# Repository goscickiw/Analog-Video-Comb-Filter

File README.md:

# Analog-Video-Comb-Filter
Analog Composite Video to S-Video comb filter board using SAA4960, SAA4961 or SAA4963 integrated circuit.

## **WARNING**
**This project uses end-of-life components that are no longer manufactured. If you want to build this, make sure that you can obtain all components before starting. Used or new-old-stock parts can sometimes be found online.**

## Description

This is a fully analog alternative to digital comb filters such as Extron YCS Transcoder or YCS 100. [That doesn't mean it will give better results though](#image-comparison---no-filter-lc-filter-and-comb-filters). I just made it because I didn't find any fully analog device like that on the market and I wanted one.

The comb filter is used to convert a composite video signal into an S-Video (Y/C) signal. Comb filters are much better than passive LC filters usually built into composite video displays, as they can preserve the frequencies of luminance that overlap with chrominance, providing higher image detail while removing dot crawl, and remove those overlapping luminance frequencies from the chrominance signal which reduces color artifacts.

When using the SAA4960 integrated circuit, PAL B, D, G, H and I systems are supported.

SAA4961 provides aditional support for PAL M, N and NTSC M systems.

When using the SAA4963 integrated circuit, only the NTSC M system is supported.

The board is designed to fit inside a KRADEX Z-76 enclosure.

### Circuit description

A composite video signal is fed in through an RCA connector (J4). The signal is terminated with a 75 ohm resistor and fed to U3 (or U7), U4 and U6 through 100 nF capacitors.

The LM1881 sync separator (U6) uses the composite video signal to generate a burst gate signal. The burst gate signal passes through a 74HC04 inverter (U5) to the MC44144 subcarrier PLL (U4).

U4 uses the composite video signal and the burst gate signal to generate a subcarrier frequency synchronized to the colorburst of the composite video signal. This subcarrier signal is then passed to the FSC input of U3/U7.

The SAA4960/61/63 comb filter (U3 or U7) is fed with the composite video signal and the synchronized subcarrier signal. The jumpers SYS1 and SYS2 set the video standard, and the jumper LPF can be used to disable the input low-pass filter. This circuit outputs filtered luminance and chrominance signals and a delayed composite video passthrough signal (when using SAA4963, the CVBYP jumper has to be shorted to allow non-delayed composite video passthrough). Those signals are then fed to the output amplifiers.

The AD813 triple op-amp (U2) is used for the output amplifiers. The output signals from the SAA4960/61[^1] are DC-biased by around 1V, so a non-rail-to-rail op-amp like the AD813 is viable. The gain can be adjusted from approx. 1,5x to 2,5x with RV1, RV2 and RV3.

## Pictures

| Assembled rev.2 devices (PAL and NTSC)               | Completed, operating device in enclosure                     |
| ---------------------------------------------------- | ------------------------------------------------------------ |
|  |  |

### Image comparison - no filter, LC filter and comb filters

<table>
  <tr>
    <th width="50%">No filter</th>
    <th width="50%">LC filter</th>
  </tr>
  <tr>
    <td>Luminance detail is preserved, but dot crawl is visible across the entire picture.</td>
    <td>Dot crawl is mostly removed, but luminance loses some sharpness, and higher frequency luminance components (responsible for sharpness) are left in chrominance causing color artifacts.</td>
  </tr>
  <tr>
    <td></td>
    <td></td>
  </tr>
  <tr>
    <td></td>
    <td></td>
  </tr>
  <tr>
    <th>This analog comb filter</th>
    <th>MC141627 digital comb filter (for comparison, Extron YCS transcoder)</th>
  </tr>
  <tr>
    <td>Dot crawl is mostly removed and luminance sharpness is mostly preserved. Higher frequency luminance components are properly separated from chrominance.</td>
    <td>More effective than the analog comb filter.</td>
  </tr>
  <tr>
    <td></td>
    <td></td>
  </tr>
</table>

<details>
  <summary>Monochrome image comparison</summary>
  <table>
    <tr>
      <th width="50%">No filter</th>
      <th width="50%">LC filter</th>
    </tr>
    <tr>
      <td>Luminance detail is preserved, but dot crawl is visible in colored sections.</td>
      <td>Dot crawl is mostly removed, but luminance loses some sharpness.</td>
    </tr>
    <tr>
      <td></td>
      <td></td>
    </tr>
    <tr>
      <td></td>
      <td></td>
    </tr>
    <tr>
      <th>This analog comb filter</th>
      <th>MC141627 digital comb filter (for comparison, Extron YCS transcoder)</th>
    </tr>
    <tr>
      <td>Dot crawl is mostly removed and luminance sharpness is mostly preserved.</td>
      <td>More effective than the analog comb filter.</td>
    </tr>
    <tr>
      <td></td>
      <td></td>
    </tr>
  </table>
</details>

## LEDs

D1 shows that the device is receiving power.

D2 shows that the comb filter is operating (U3 is in COMB mode). I'm not sure if U3 will ever *not* be in COMB mode when used in this circuit, so this LED might be unnecessary. SAA4963 does not have the output needed by this LED, so if it is used, then R19, R20, D2 and Q1 can be left unpopulated.

## REFDL filter capacitors

When using SAA4960 or SAA4961, install C24 and C26, and leave C31 and C32 unpopulated.

When using SAA4963, install C31 and C32, and leave C24 and C26 unpopulated.

## Solder jumper settings

### Standard selection jumpers (SYS1, SYS2)

SAA4961 only. When using SAA4960, SYS1 and SYS2 jumpers should be left open. When using SAA4963, the jumpers are not connected.

Appropriate crystal for the subcarrier oscillator should be installed depending on the jumper setting. If the standard is going to be changed frequently, it may be possible to install a socket for the crystal, however it should be taken into account that MC44144 is sensitive to additional capacitance at the crystal.

| Standard      | SYS1  | SYS2  | Crystal required | 
| ------------- | ----- | ----- | ---------------- |
| PAL B/D/G/H/I | Open  | Open  | 17,734475 MHz    |
| PAL M         | Open  | Short | 14,302444 MHz    |
| PAL N         | Short | Open  | 14,328225 MHz    |
| NTSC M        | Short | Short | 14,31818 MHz     |

### Low pass filter jumper (LPF)

The SAA4960, SAA4961 and SAA4963 integrated circuits have a built-in low-pass filter on the composite video input. With SAA4960 and SAA4961, this filter can be disabled by shorting the LPF jumper, but it's recommended to leave it on. With SAA4963, the jumper is not connected and the filter is always on.

| LPF   | Filter mode     |
| ----- | --------------- |
| Open  | Filter enabled  |
| Short | Filter disabled |

### Composite video passthrough jumper (CVBYP)

SAA4963 doesn't have a composite video output, so the CVBYP jumper was provided for composite video passthrough. When the jumper is shorted, the video signal for composite video output is taken from pin 13 (composite video input) of SAA4963. The DC bias for the output amplifier is provided by the clamping circuit inside SAA4963. Do not install R12 to avoid additional load to the clamping circuit. This configuration has not been tested and may not work correctly. Leave the jumper open if shorting it causes issues for the comb filter.

**WARNING: This jumper must never be shorted if using SAA4960/61.**

| CVBYP | Usage                          |
| ----- | ------------------------------ |
| Open  | When using SAA4960 or SAA4961. |
| Short | When using SAA4963.            |

## Adjustment

After assembly, including setting the jumpers and installing the correct crystal depending on the analog video standard, the variable capacitor C17 will have to be adjusted so that the PLL locks correctly to the color subcarrier and the loop control voltage is centered.

Use the following procedure for adjustment:

1. Connect an EBU (for PAL) or SMPTE (for NTSC) color bar signal from a good quality reference source to the composite video input.
2. Connect a 10x oscillososcope probe to U4 pin 3 (phase detector output loop filter). Use AC coupling, 200 mV/div vertical scale, and 100 µs/div timebase.
3. Here are the reference pictures needed for the following steps:

<details>
  <summary>PAL waveforms</summary>
  <table>
    <tr>
      <th width="33%">Not locked</th>
      <th width="33%">Locked, not adjusted</th>
      <th width="33%">Best adjustment</th>
    </tr>
    <tr>
      <td></td>
      <td><br/></td>
      <td></td>
    </tr>
  </table>
</details>

<details>
  <summary>NTSC waveforms</summary>
  <table>
    <tr>
      <th width="33%">Not locked</th>
      <th width="33%">Locked, not adjusted</th>
      <th width="33%">Best adjustment</th>
    </tr>
    <tr>
      <td></td>
      <td><br/></td>
      <td></td>
    </tr>
  </table>
</details>

4. Follow the flow chart below:

```mermaid
flowchart LR
  A{Able to obtain waveform shown in <b>Best&nbsp;adjustment</b> by adjusting C17?} -- Yes --> B([PLL correctly adjusted.]);
  A -->|No| C{"PLL able to lock (one of <b>Locked,&nbsp;not&nbsp;adjusted</b> waveforms)?"};
  C -->|Yes| D{Does waveform resemble the <b>top</b> or <b>bottom</B> picture in <b>Locked,&nbsp;not&nbsp;adjusted</b>?};
  C -->|No| E["Measure frequency at U4 pin 1 (FSC output), and adjust C17 to get as close as possible to required frequency."];
  E --> F{Is the frequency higher or lower than required?};
  F -->|Higher| G[replace C17 with a higher max. value trim capacitor, or add a parallel capacitor.];
  F -->|Lower| H[replace C17 with a lower min. value trim capacitor.];
  D -->|Top| G;
  D -->|Bottom| H;
  G --> I[Adjust C17 and observe the waveform at U4 pin 3.] --> A;
  H --> I;
```

5. Set RV1, RV2, RV3 to center position. Connect the luminance, chrominance and composite outputs to an oscilloscope with 75 ohm load resistance. Luminance signal is preferred for oscilloscope trigger. Adjust RV1, RV2, RV3 to obtain the following:

<table>
  <tr>
    <th>Output</th>
    <th>Adjustment</th>
    <th>Measured value</th>
    <th>PAL</th>
    <th>NTSC</th>
  </tr>
  <tr>
    <td>Chrominance</td>
    <td>RV1</td>
    <td>Peak-peak <b>colorburst</b></td>
    <td>300 mV</td>
    <td>285,72 mV</td>
  </tr>
  <tr>
    <td>Luminance</td>
    <td>RV2</td>
    <td rowspan=2>Peak-peak voltage<br/>(sync level to 100% white level)</td>
    <td rowspan=2 colspan=2>1 V</td>
  </tr>
  <tr>
    <td>Composite</td>
    <td>RV3</td>
  </tr>
</table>

Readjustment is necessary if the crystal and the standard selection jumper settings are changed.

## Parts list

### Resistors

| Resistance | Power  | Qty |
| ---------- | ------ | --- |
| 47 Ω       | 0,25 W | 1   |
| 75 Ω       | 0,25 W | 4   |
| 470 Ω      | 0,25 W | 3   |
| 1 kΩ       | 0,25 W | 6   |
| 4,7 kΩ     | 0,25 W | 1   |
| 10 kΩ      | 0,25 W | 4   |
| 47 kΩ      | 0,25 W | 1   |
| 680 kΩ     | 0,25 W | 1   |

### Capacitors

| Capacitance | Pin pitch | Type                       | Qty |
| ----------- | --------- | -------------------------- | --- |
| 4-20 pF     | 5,08 mm   | Ceramic variable           | 1   |
| 470 pF      | 2,5 mm    | Ceramic                    | 1   |
| 1 nF        | 5 mm      | Ceramic                    | 1   |
| 100 nF      | 2,5 mm    | Ceramic                    | 18  |
| 100 μF      | 2 mm      | Electrolytic, ≥6,3V, ⌀5mm  | 6   |
| 100 μF      | 2 mm      | Electrolytic, ≥16V, ⌀5mm   | 1   |
| 220 μF      | 2,5 mm    | Electrolytic, ≥16V, ⌀6,3mm | 2   |

### Inductors

| Inductance | Max. Current | Exact part        | Qty |
| ---------- | ------------ | ----------------- | --- |
| 22 μH      | 0,285 A      | Ferrocore DLA22-N | 6   |

### Semiconductors

| Type           | Model     | Qty |
| -------------- | --------- | --- |
| LED            | 3mm Green | 1   |
| LED            | 3mm Red   | 1   |
| NPN Transistor | BC548     | 1   |

### Integrated circuits

| Model                         | Package                               | Qty |
| ----------------------------- | ------------------------------------- | --- |
| L7805                         | TO220                                 | 1   |
| AD813 or AD8044               | DIP14                                 | 1   |
| SAA4960 or SAA4961 or SAA4963 | DIP28 (SAA4960/61) or DIP20 (SAA4963) | 1   |
| MC44144                       | DIP8                                  | 1   |
| 74HC04                        | DIP14                                 | 1   |
| LM1881                        | DIP8                                  | 1   |

### Other

| Type               | Model                           | Qty |
| ------------------ | ------------------------------- | --- |
| Potentiometer      | PIHER PT10LH-1K                 | 3   |
| Crystal            | HC-49U, depends on video system | 1   |
| RCA Connector      | Keystone Electronics 973        | 2   |
| Mini-DIN Connector | MDC-204, unshielded             | 1   |
| DC Barrel Jack     | Generic 5,5/2,5mm               | 1   |
| Enclosure          | KRADEX Z-76                     | 1   |

## License

This work is licensed under CC BY-SA 4.0 license.

[^1]: SAA4963 has not been tested as I don't have one yet.

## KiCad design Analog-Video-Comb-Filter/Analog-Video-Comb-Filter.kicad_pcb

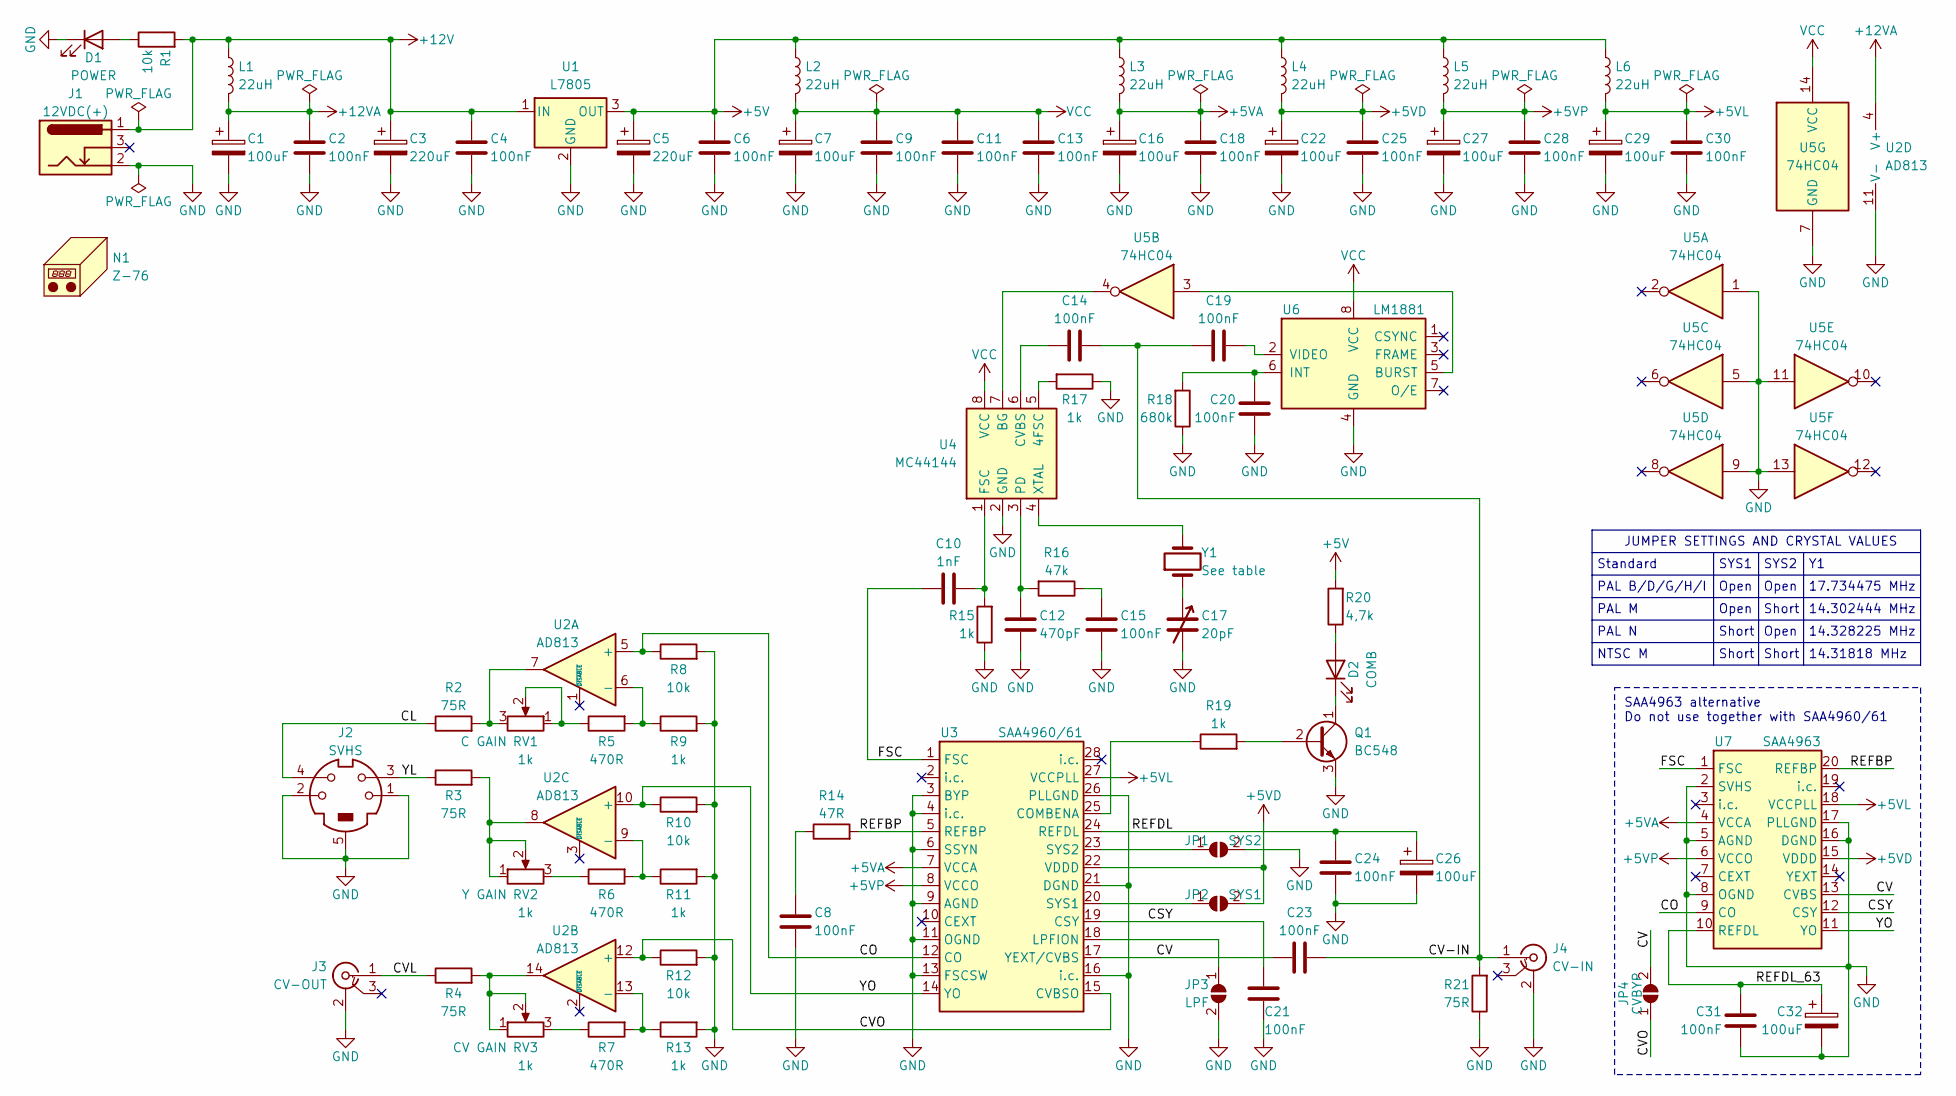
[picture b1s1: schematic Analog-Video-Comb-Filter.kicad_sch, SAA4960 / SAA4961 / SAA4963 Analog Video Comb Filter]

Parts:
C1, C7, C16, C22, C26, C27, C29, C32: 100uF; CP_Radial_D5.0mm_P2.00mm
C2, C4, C6, C8, C9, C11, C13, C14, C15, C18, C19, C20, C21, C23, C24, C25, C28, C30, C31: 100nF; C_Disc_D5.0mm_W2.5mm_P2.50mm
C3, C5: 220uF; CP_Radial_D6.3mm_P2.50mm
C10: 1nF; C_Disc_D5.0mm_W2.5mm_P5.00mm
C12: 470pF; C_Disc_D5.0mm_W2.5mm_P2.50mm
C17: 20pF; C_Trimmer_D6.0mm_P5.08mm
D1: POWER; LED_D3.0mm
D2: COMB; LED_D3.0mm
J1: 12VDC(+); BarrelJack_Horizontal
J2: SVHS; MDC-204
J3: CV-OUT; Keystone_973
J4: CV-IN; Keystone_973
JP1: SYS2; SolderJumper-2_P1.3mm_Open_RoundedPad1.0x1.5mm
JP2: SYS1; SolderJumper-2_P1.3mm_Open_RoundedPad1.0x1.5mm
JP3: LPF; SolderJumper-2_P1.3mm_Open_RoundedPad1.0x1.5mm
JP4: CVBYP; SolderJumper-2_P1.3mm_Open_RoundedPad1.0x1.5mm
L1, L2, L3, L5: 22uH; L_Axial_L5.3mm_D2.2mm_P7.62mm_Horizontal_Vishay_IM-1
L4, L6: 22uH; L_Axial_L5.3mm_D2.2mm_P2.54mm_Vertical_Vishay_IM-1
N1: Z-76
Q1: BC548; TO-92_Inline_Wide
R1, R8, R10, R12: 10k; R_Axial_DIN0207_L6.3mm_D2.5mm_P7.62mm_Horizontal
R2, R3, R4, R21: 75R; R_Axial_DIN0207_L6.3mm_D2.5mm_P7.62mm_Horizontal
R5, R6, R7: 470R; R_Axial_DIN0207_L6.3mm_D2.5mm_P7.62mm_Horizontal
R9, R11, R13, R15, R17, R19: 1k; R_Axial_DIN0207_L6.3mm_D2.5mm_P7.62mm_Horizontal
R14: 47R; R_Axial_DIN0207_L6.3mm_D2.5mm_P7.62mm_Horizontal
R16: 47k; R_Axial_DIN0207_L6.3mm_D2.5mm_P7.62mm_Horizontal
R18: 680k; R_Axial_DIN0207_L6.3mm_D2.5mm_P7.62mm_Horizontal
R20: 4,7k; R_Axial_DIN0207_L6.3mm_D2.5mm_P7.62mm_Horizontal
RV1, RV2, RV3: 1k; Potentiometer_Piher_PT-10-H01_Horizontal
U1: L7805; TO-220-3_Horizontal_TabDown
U2: AD813; DIP-14_W7.62mm_Socket
U3: SAA4960/61; DIP-28_W15.24mm_Socket
U4: MC44144; DIP-8_W7.62mm_Socket
U5: 74HC04; DIP-14_W7.62mm_Socket
U6: LM1881; DIP-8_W7.62mm_Socket
U7: SAA4963; DIP-20_W7.62mm_Socket
Y1: See table; Crystal_HC49-U_Vertical

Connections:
+5V: C5.1, C6.1, L2.1, L3.1, L4.2, L5.1, L6.2, R20.2, U1.3 (OUT)
+5VA: C16.1, C18.1, L3.2, U3.7 (VCCA), U7.4 (VCCA)
+5VD: C22.1, C25.1, JP2.2 (B), L4.1, U3.22 (VDDD), U7.15 (VDDD)
+5VL: C29.1, C30.1, L6.1, U3.27 (VCCPLL), U7.18 (VCCPLL)
+5VP: C27.1, C28.1, L5.2, U3.8 (VCCO), U7.6 (VCCO)
+12V: C3.1, C4.1, J1.1, L1.1, R1.2, U1.1 (IN)
+12VA: C1.1, C2.1, L1.2, U2.4 (V+)
/CL: J2.4, R2.1
/CO: R8.1, U2.5 (+), U3.12 (CO), U7.9 (CO)
/CSY: C21.1, U3.19 (CSY), U7.12 (CSY)
/CV: C23.1, JP4.2 (B), U3.17 (YEXT/CVBS), U7.13 (CVBS)
/CV-IN: C14.2, C19.1, C23.2, J4.1 (In), R21.2
/CVL: J3.1 (In), R4.1
/CVO: JP4.1 (A), R12.1, U2.12 (+), U3.15 (CVBSO)
/FSC: C10.1, U3.1 (FSC), U7.1 (FSC)
/REFBP: R14.2, U3.5 (REFBP), U7.20 (REFBP)
/REFDL: C24.1, C26.1, U3.24 (REFDL)
/REFDL_63: C31.1, C32.1, U7.10 (REFDL)
/YL: J2.3, R3.1
/YO: R10.1, U2.10 (+), U3.14 (YO), U7.11 (YO)
GND: C1.2, C2.2, C3.2, C4.2, C5.2, C6.2, C7.2, C8.2, C9.2, C11.2, C12.2, C13.2, C15.2, C16.2, C17.2, C18.2, C20.2, C21.2, C22.2, C24.2, C25.2, C26.2, C27.2, C28.2, C29.2, C30.2, C31.2, C32.2, D1.1 (K), J1.2, J2.1, J2.2, J2.5, J3.2 (Ext), J4.2 (Ext), JP1.2 (B), JP3.2 (B), Q1.3 (E), R8.2, R9.2, R10.2, R11.2, R12.2, R13.2, R15.1, R17.1, R18.1, R21.1, U1.2 (GND), U2.11 (V-), U3.3 (BYP), U3.4 (i.c.), U3.6 (SSYN), U3.9 (AGND), U3.11 (OGND), U3.13 (FSCSW), U3.16 (i.c.), U3.21 (DGND), U3.26 (PLLGND), U4.2 (GND), U5.1, U5.5, U5.7 (GND), U5.9, U5.11, U5.13, U6.4 (GND), U7.2 (SVHS), U7.5 (AGND), U7.8 (OGND), U7.16 (DGND), U7.17 (PLLGND)
unnamed: C8.1, R14.1
unnamed: C15.1, R16.1
unnamed: C17.1, Y1.1
unnamed: D1.2 (A), R1.1
unnamed: D2.2 (A), R20.1
unnamed: D2.1 (K), Q1.1 (C)
unnamed: JP1.1 (A), U3.23 (SYS2)
unnamed: JP2.1 (A), U3.20 (SYS1)
unnamed: JP3.1 (A), U3.18 (LPFION)
unnamed: Q1.2 (B), R19.2
unnamed: R2.2, RV1.3, U2.7
unnamed: R3.2, RV2.1, RV2.2, U2.8
unnamed: R4.2, RV3.1, RV3.2, U2.14
unnamed: R5.1, RV1.1, RV1.2
unnamed: R6.1, RV2.3
unnamed: R7.1, RV3.3
unnamed: R5.2, R9.1, U2.6 (-)
unnamed: R7.2, R13.1, U2.13 (-)
unnamed: R6.2, R11.1, U2.9 (-)
unnamed: R19.1, U3.25 (COMBENA)
unnamed: R17.2, U4.5 (4FSC)
unnamed: U4.7 (BG), U5.4
unnamed: C14.1, U4.6 (CVBS)
unnamed: C10.2, R15.2, U4.1 (FSC)
unnamed: C12.1, R16.2, U4.3 (PD)
unnamed: U4.4 (XTAL), Y1.2
unnamed: U5.3, U6.5 (BURST)
unnamed: C20.1, R18.2, U6.6 (INT)
unnamed: C19.2, U6.2 (VIDEO)
VCC: C7.1, C9.1, C11.1, C13.1, L2.2, U4.8 (VCC), U5.14 (VCC), U6.8 (VCC)

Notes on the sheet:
SYS2
Short
PAL N
PAL M
SAA4963 alternative Do not use together with SAA4960/61
SYS1
14.302444 MHz
Open
14.328225 MHz
17.734475 MHz
NTSC M
14.31818 MHz
PAL B/D/G/H/I
Standard
JUMPER SETTINGS AND CRYSTAL VALUES

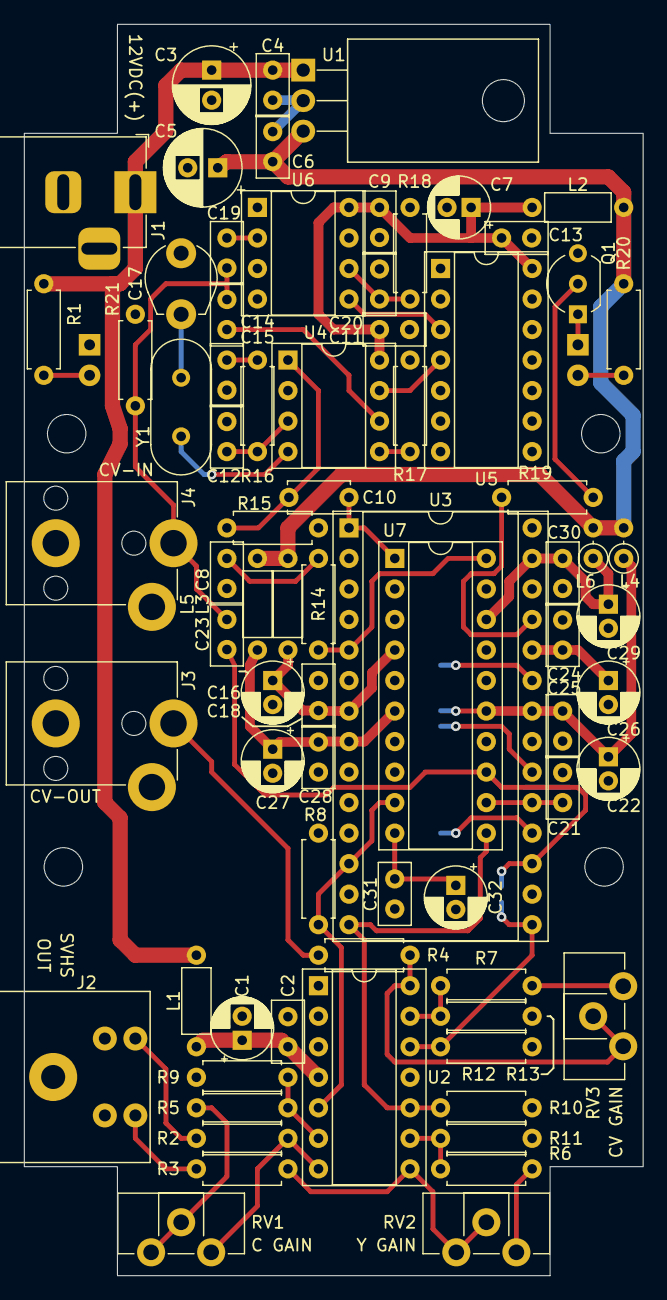
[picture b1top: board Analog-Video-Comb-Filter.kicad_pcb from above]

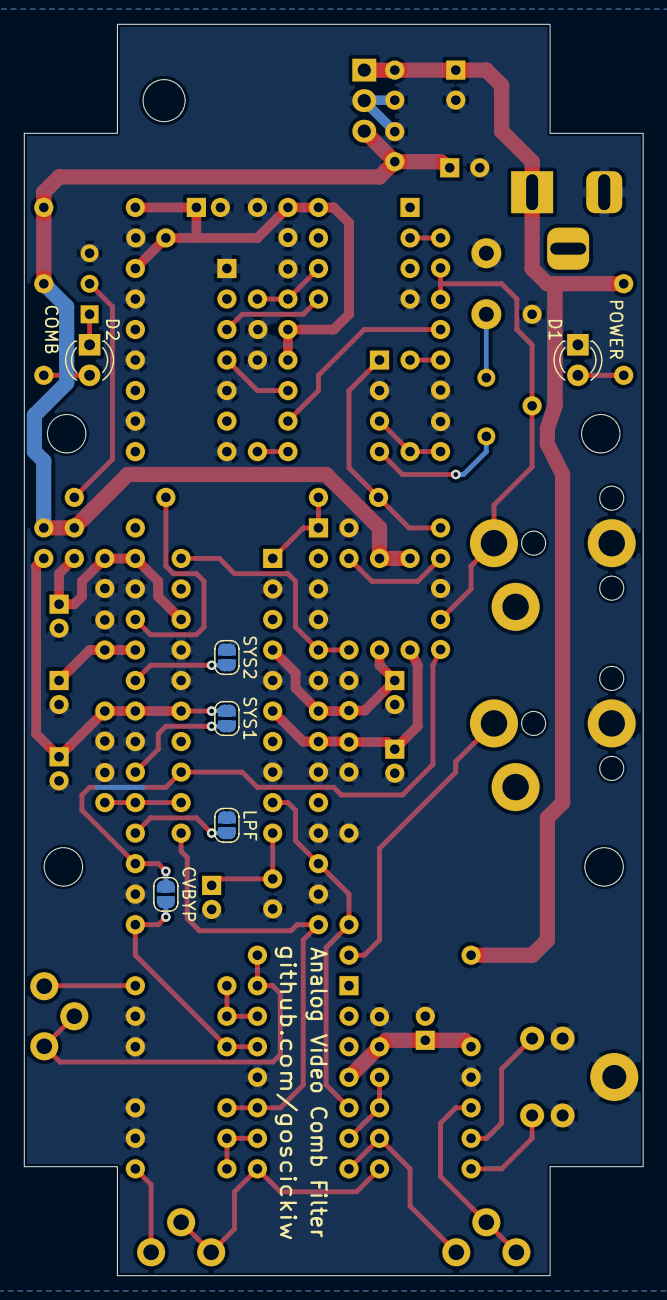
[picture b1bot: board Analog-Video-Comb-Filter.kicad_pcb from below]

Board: 2 copper layers, 51.5 x 104.1 mm, 82 parts (6 on the bottom side), 51 nets.

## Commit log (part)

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2024-08-31 Replaced RCA connector footprint, added gerber files, fixed README
2024-08-31 Better comparison images including LC filter
2024-08-31 Further improved comparison images
2024-09-28 Added alternative footprint for SAA4963
2024-09-28 Added description of setup for tuning the PLL
2024-09-28 Changed C24 to C21 as a result of KiCad auto-renumber
2024-09-28 Gerber files for SAA4963 version
2025-07-25 Better PLL adjustment method
2025-07-25 Fix typo
2025-11-16 Improved PCB layout, readme improvements
    - Minimized (unfortunately not eliminated) ground plane interruptions under signal traces.
    - Added dedicated location for SAA4963 alternative footprint REFDL filter capacitors. This way they are not far away and the trace to them is not in the way of other traces.
    - Better routing of some traces around the SAA4963 alternative footprint.
    - More accurate description of PLL tuning method, with pictures.
    - Better quality comparison pictures.
    - Various other readme fixes.
2026-02-14 Corrected mistake in CVBYP jumper description
    The video input of the comb filter IC has a clamping circuit that provides a DC bias voltage, so adding extra DC biasing resistors might cause problems.
2026-02-14 New output amplifier design
    The BJT amplifiers have been replaced with high bandwidth rail-to-rail operational amplifiers. This should resolve the issue of the signal becoming malformed when load is connected through a capacito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
2026-02-21 Fixed numbering mistakes on PCB, fixed BOM, added color comparison images
    - Fixed incorrect R12, R13, R18 and R19 numbers on PCB.
    - Removed 560 ohm resistors from parts list.
    - Changed 2.2k resistor to 1k as its resistance wasn't critical, now there's one less different part.
    - Set solder jumpers and some mutually exclusive parts to be excluded from BOM generation.
    - Renamed documentation folder to pdf.
    - Added PCB layers in PDF form.
2026-02-21 More detailed comparison image descriptions
2026-02-21 Update README.md
    Reformatted comparison image tables as HTML so that the columns are equal width.
2026-02-21 Replaced comparison images
    The previous comparison images had an issue with contrast, so I had to make them again with a fixed contrast value in the capture program.
2026-02-21 AD813 tested and working, added circuit diagram to README
2026-02-26 NTSC tested, more precise adjustment procedure
